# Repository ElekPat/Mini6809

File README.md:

This is my Kicad version of http://www.christle.us/index.php?P=1

I replaced the SIP resistor network with traditional through hole resistors.

I added a blue user led connected to PA1 and I added a reset button.

I removed the 5V regulator and provided a standard 2 pin JST connector for external +5V supply (not normally required as the Serial socket connected to a FTDI like USB to serial adapter will provide the necessary +5V).

For assembling source files, I use http://john.ccac.rwth-aachen.de:8000/as/ (Macro Assembler compatible with multiple target CPUs, see my other projects)

Use the following 2 command lines to generate a S19 file:
 - asw.exe -cpu 6809 -L source.asm
 - p2hex.exe source.p +5 -k -F Moto

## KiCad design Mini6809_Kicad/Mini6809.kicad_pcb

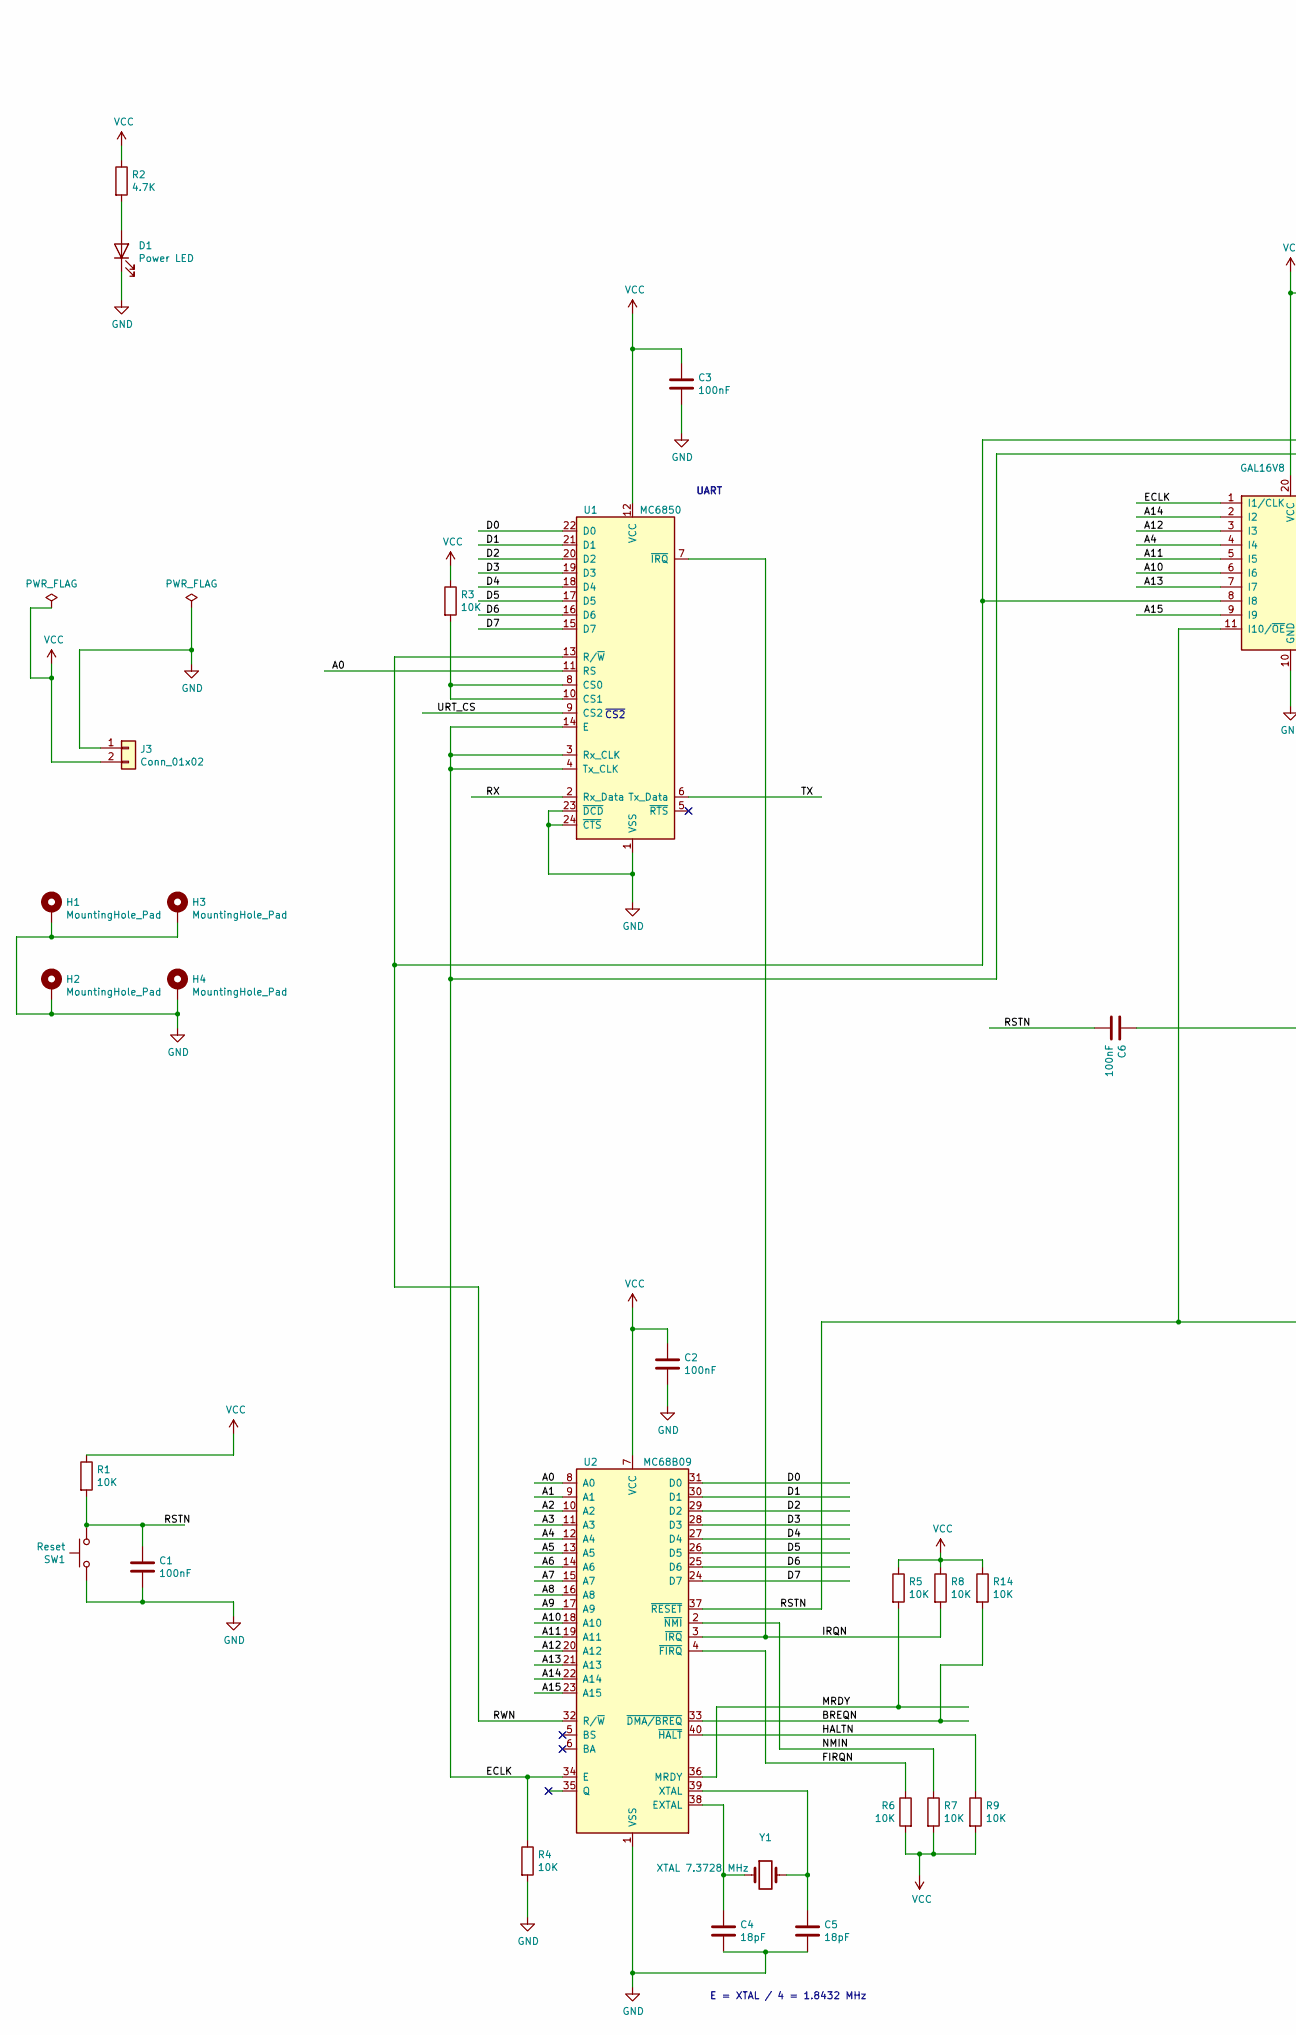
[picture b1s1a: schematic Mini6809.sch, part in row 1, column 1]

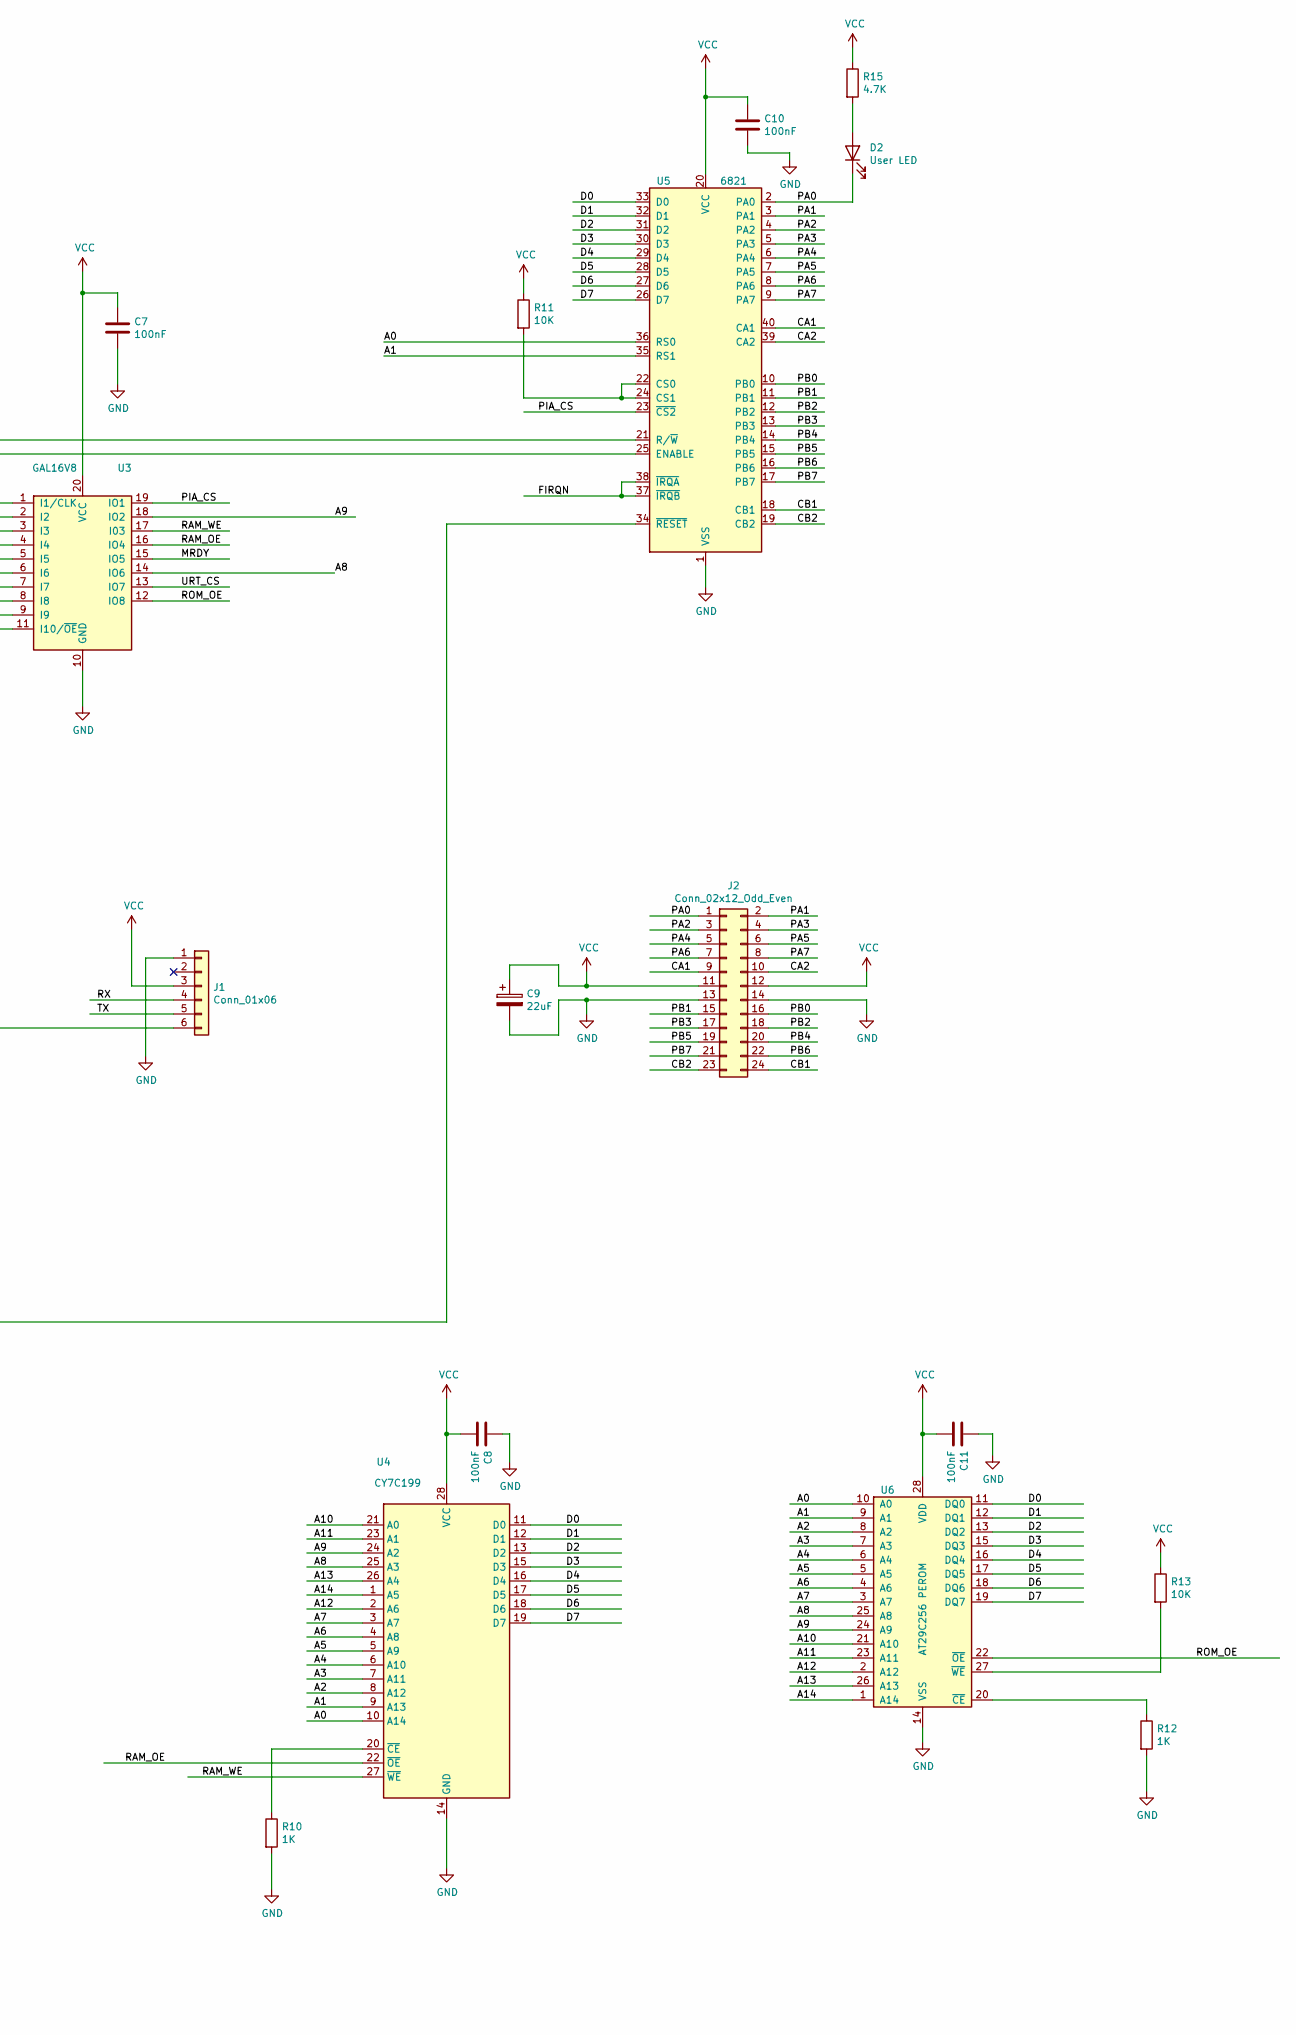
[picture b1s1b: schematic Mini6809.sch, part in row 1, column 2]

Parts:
C1, C2, C3, C6, C7, C8, C10, C11: 100nF; C_Disc_D4.3mm_W1.9mm_P5.00mm
C4, C5: 18pF; C_Disc_D3.0mm_W1.6mm_P2.50mm
C9: 22uF; CP_Radial_Tantal_D5.0mm_P2.50mm
D1: Power LED; LED_D3.0mm
D2: User LED; LED_D3.0mm
H1, H2, H3, H4: MountingHole_Pad; MountingHole_3mm_Pad
J1: Conn_01x06; PinHeader_1x06_P2.54mm_Vertical
J2: Conn_02x12_Odd_Even; PinHeader_2x12_P2.54mm_Vertical
J3: Conn_01x02; JST_XH_B2B-XH-AM_1x02_P2.50mm_Vertical
R1, R3, R4, R5, R6, R7, R8, R9, R11, R13, R14: 10K; R_Axial_DIN0207_L6.3mm_D2.5mm_P7.62mm_Horizontal
R2, R15: 4.7K; R_Axial_DIN0207_L6.3mm_D2.5mm_P7.62mm_Horizontal
R10, R12: 1K; R_Axial_DIN0207_L6.3mm_D2.5mm_P7.62mm_Horizontal
SW1: Reset; SW_PUSH_6mm
U1: MC6850; DIP-24_W15.24mm
U2: MC68B09; DIP-40_W15.24mm
U3: GAL16V8; DIP-20_W7.62mm
U4: CY7C199; DIP-28_W7.62mm
U5: 6821; DIP-40_W15.24mm
U6: AT29C256 PEROM; DIP-28_W15.24mm
Y1: XTAL 7.3728 MHz; Crystal_HC49-U_Vertical

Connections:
/A0: U1.11 (RS), U2.8 (A0), U4.10 (A14), U5.36 (RS0), U6.10 (A0)
/A1: U2.9 (A1), U4.9 (A13), U5.35 (RS1), U6.9 (A1)
/A2: U2.10 (A2), U4.8 (A12), U6.8 (A2)
/A3: U2.11 (A3), U4.7 (A11), U6.7 (A3)
/A4: U2.12 (A4), U3.4 (I4), U4.6 (A10), U6.6 (A4)
/A5: U2.13 (A5), U4.5 (A9), U6.5 (A5)
/A6: U2.14 (A6), U4.4 (A8), U6.4 (A6)
/A7: U2.15 (A7), U4.3 (A7), U6.3 (A7)
/A8: U2.16 (A8), U3.14 (IO6), U4.25 (A3), U6.25 (A8)
/A9: U2.17 (A9), U3.18 (IO2), U4.24 (A2), U6.24 (A9)
/A10: U2.18 (A10), U3.6 (I6), U4.21 (A0), U6.21 (A10)
/A11: U2.19 (A11), U3.5 (I5), U4.23 (A1), U6.23 (A11)
/A12: U2.20 (A12), U3.3 (I3), U4.2 (A6), U6.2 (A12)
/A13: U2.21 (A13), U3.7 (I7), U4.26 (A4), U6.26 (A13)
/A14: U2.22 (A14), U3.2 (I2), U4.1 (A5), U6.1 (A14)
/A15: U2.23 (A15), U3.9 (I9)
/BREQN: R14.2, U2.33 (~DMA/BREQ)
/CA1: J2.9, U5.40 (CA1)
/CA2: J2.10, U5.39 (CA2)
/CB1: J2.24, U5.18 (CB1)
/CB2: J2.23, U5.19 (CB2)
/D0: U1.22 (D0), U2.31 (D0), U4.11 (D0), U5.33 (D0), U6.11 (DQ0)
/D1: U1.21 (D1), U2.30 (D1), U4.12 (D1), U5.32 (D1), U6.12 (DQ1)
/D2: U1.20 (D2), U2.29 (D2), U4.13 (D2), U5.31 (D2), U6.13 (DQ2)
/D3: U1.19 (D3), U2.28 (D3), U4.15 (D3), U5.30 (D3), U6.15 (DQ3)
/D4: U1.18 (D4), U2.27 (D4), U4.16 (D4), U5.29 (D4), U6.16 (DQ4)
/D5: U1.17 (D5), U2.26 (D5), U4.17 (D5), U5.28 (D5), U6.17 (DQ5)
/D6: U1.16 (D6), U2.25 (D6), U4.18 (D6), U5.27 (D6), U6.18 (DQ6)
/D7: U1.15 (D7), U2.24 (D7), U4.19 (D7), U5.26 (D7), U6.19 (DQ7)
/ECLK: R4.1, U1.3 (Rx_CLK), U1.4 (Tx_CLK), U1.14 (E), U2.34 (E), U3.1 (I1/CLK), U5.25 (ENABLE)
/FIRQN: R6.1, U2.4 (~FIRQ), U5.37 (~IRQB), U5.38 (~IRQA)
/HALTN: R9.1, U2.40 (~HALT)
/IRQN: R8.2, U1.7 (~IRQ), U2.3 (~IRQ)
/MRDY: R5.2, U2.36 (MRDY), U3.15 (IO5)
/NMIN: R7.1, U2.2 (~NMI)
/PA0: D2.1 (K), J2.1, U5.2 (PA0)
/PA1: J2.2, U5.3 (PA1)
/PA2: J2.3, U5.4 (PA2)
/PA3: J2.4, U5.5 (PA3)
/PA4: J2.5, U5.6 (PA4)
/PA5: J2.6, U5.7 (PA5)
/PA6: J2.7, U5.8 (PA6)
/PA7: J2.8, U5.9 (PA7)
/PB0: J2.16, U5.10 (PB0)
/PB1: J2.15, U5.11 (PB1)
/PB2: J2.18, U5.12 (PB2)
/PB3: J2.17, U5.13 (PB3)
/PB4: J2.20, U5.14 (PB4)
/PB5: J2.19, U5.15 (PB5)
/PB6: J2.22, U5.16 (PB6)
/PB7: J2.21, U5.17 (PB7)
/PIA_CS: U3.19 (IO1), U5.23 (~CS2)
/RAM_OE: U3.16 (IO4), U4.22 (~OE~)
/RAM_WE: U3.17 (I03), U4.27 (~WE~)
/ROM_OE: U3.12 (IO8), U6.22 (~OE~)
/RSTN: C1.1, C6.2, R1.2, SW1.1, U2.37 (~RESET), U3.11 (I10/~OE~), U5.34 (~RESET)
/RWN: U1.13 (R/~W), U2.32 (R/~W), U3.8 (I8), U5.21 (R/~W)
/RX: J1.4, U1.2 (Rx_Data)
/TX: J1.5, U1.6 (Tx_Data)
/URT_CS: U1.9 (CS2), U3.13 (IO7)
GND: C1.2, C2.2, C3.2, C4.2, C5.2, C7.2, C8.1, C9.2, C10.2, C11.1, D1.1 (K), H1.1, H2.1, H3.1, H4.1, J1.1, J2.13, J2.14, J3.1, R4.2, R10.2, R12.2, SW1.2, U1.1 (VSS), U1.23 (~DCD), U1.24 (~CTS), U2.1 (VSS), U3.10 (GND), U4.14 (GND), U5.1 (VSS), U6.14 (VSS)
unnamed: C4.1, U2.38 (EXTAL), Y1.1
unnamed: C5.1, U2.39 (XTAL), Y1.2
unnamed: C6.1, J1.6
unnamed: D1.2 (A), R2.2
unnamed: D2.2 (A), R15.2
unnamed: R3.2, U1.8 (CS0), U1.10 (CS1)
unnamed: R10.1, U4.20 (~CE~)
unnamed: R11.2, U5.22 (CS0), U5.24 (CS1)
unnamed: R12.1, U6.20 (~CE~)
unnamed: R13.2, U6.27 (~WE~)
VCC: C2.1, C3.1, C7.1, C8.2, C9.1, C10.1, C11.2, J1.3, J2.11, J2.12, J3.2, R1.1, R2.1, R3.1, R5.1, R6.2, R7.2, R8.1, R9.2, R11.1, R13.1, R14.1, R15.1, U1.12 (VCC), U2.7 (VCC), U3.20 (VCC), U4.28 (VCC), U5.20 (VCC), U6.28 (VDD)

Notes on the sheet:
E = XTAL / 4 = 1.8432 MHz
~CS2
UART

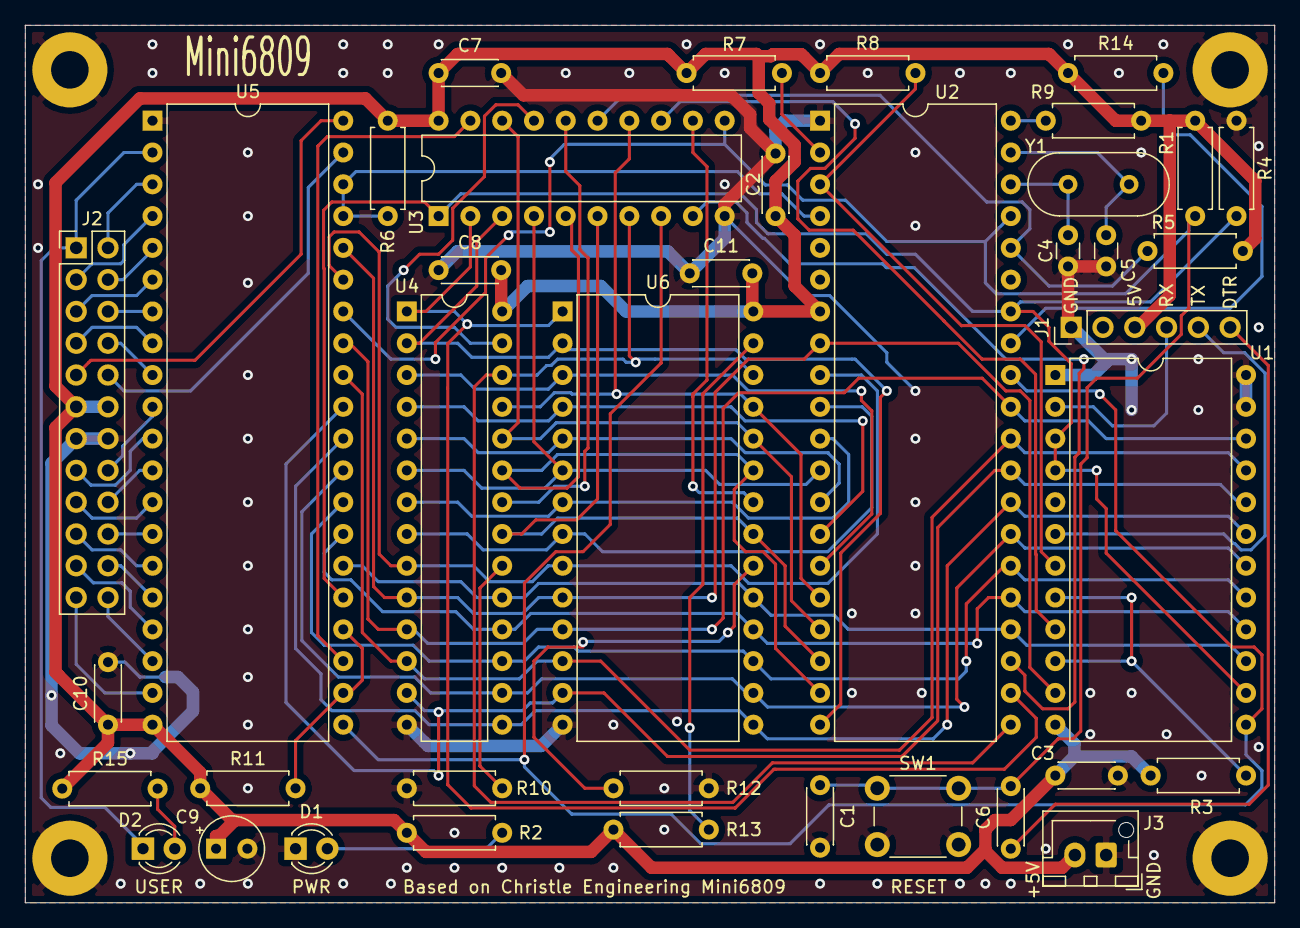
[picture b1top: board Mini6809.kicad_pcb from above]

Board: 2 copper layers, 99.8 x 70.1 mm, 43 parts (0 on the bottom side), 72 nets.

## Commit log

2023-04-11 Add Pictures via upload
2023-04-11 Add Kicad files
2023-04-11 Add Schematics in PDF format
